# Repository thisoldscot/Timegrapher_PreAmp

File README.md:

# Timegrapher PreAmp

[![CC BY-NC-SA 4.0][cc-by-nc-sa-shield]][cc-by-nc-sa]

## About the Project

|  |
| :-----------------------------------------------------------------------------------------------------------: |

Timegrapher PreAmp is the **through-hole** piezo preamplifier board for the
Timegrapher Studio wristwatch timegrapher. It conditions the faint escapement
signal from the piezo pickup and feeds the I²S ADC on the
[carrier HAT](https://github.com/thisoldscot/Timegrapher_Hat). This is the
hand-solderable variant; an SMD version lives in
[Timegrapher_PreAmpSMD](https://github.com/thisoldscot/Timegrapher_PreAmpSMD).
Designed in KiCad. See [DESIGN.md](DESIGN.md) and [BOM.md](BOM.md).

---

## Repository Contents

This repository contains the KiCad design and production files:

- **`TimegrapherPreamp.kicad_pro` / `.kicad_sch` / `.kicad_pcb`** — KiCad project.
- **`Preamp.kicad_sym` / `sym-lib-table`** — schematic symbols.
- **`Production/`** — Gerbers, drill files, and the fabrication zip.
- **`TimegrapherPreamp.step`** — 3D model of the assembled board.
- **`TimegrapherPreamp_sch.pdf`** — schematic PDF.
- **`gen_sch.py` / `gen_pcb.py`** — scripts used to generate the design.
- **`BOM.md`** — bill of materials. **`DESIGN.md`** — design notes.

Refer to the `CHANGELOG.md` for details about updates between versions.

---

## Timegrapher project

Timegrapher Studio is split across several repositories:

| Repository | Contents |
| --- | --- |
| [Timegrapher_OS](https://github.com/thisoldscot/Timegrapher_OS) | Desktop application |
| [Timegrapher_App](https://github.com/thisoldscot/Timegrapher_App) | Mobile companion app |
| [Timegrapher_Firmware](https://github.com/thisoldscot/Timegrapher_Firmware) | ESP32 device firmware |
| [Timegrapher_Hat](https://github.com/thisoldscot/Timegrapher_Hat) | Carrier HAT (PCB) |
| [Timegrapher_PreAmp](https://github.com/thisoldscot/Timegrapher_PreAmp) | Piezo preamp (through-hole) (this repo) |
| [Timegrapher_PreAmpSMD](https://github.com/thisoldscot/Timegrapher_PreAmpSMD) | Piezo preamp (SMD) |
| [Timegrapher_Stand](https://github.com/thisoldscot/Timegrapher_Stand) | 3D-printed stand & fixtures |

---

## Learn More

### Documentation

Build notes, BOM, and assembly guides can be found here:
[ThisOldScot Docs](https://thisoldscot.com)
<!-- TODO: replace with the real docs URL when live -->

### ThisOldScot Community

ThisOldScot Community is a great space for the maker community — get answers to
your questions and solutions for our projects there.
<!-- TODO: add the real community/forum URL -->

### ThisOldScot Discord

Another option to get help and advice from other makers via the ThisOldScot Discord.
<!-- TODO: add the real Discord invite URL -->

---

## Contributing

Contributions are welcome! Here's how you can get involved:

- Submit pull requests to enhance the design or fix issues.
- Report bugs or problems by opening an issue.

We encourage community collaboration to make this project even better.

---

## About ThisOldScot

[ThisOldScot](https://thisoldscot.com) enjoys designing and making electronic
products and projects for enthusiasts, from hobbyists to professionals — boards,
sensors, hobby equipment, and anything else that catches my interest. Every
project is designed in-house and built on open-source hardware and software.

---

# Support the team
We :heart: doing research. New hardware (e.g. oscilloscopes, logic analysers,
servos, PCBs) is costly. Feel free to support us and accelerate our research.

Dev | ThisOldScot |
--- | --- |
Buy me a coffee |  |
Ko-fi |  |
<!-- TODO: add the real Buy Me a Coffee / Ko-fi URLs -->

---

## License

This work is licensed under a Creative Commons Attribution-NonCommercial-ShareAlike
4.0 International License. Read more in the LICENSE file located in this repository.

Shield: [![CC BY-NC-SA 4.0][cc-by-nc-sa-shield]][cc-by-nc-sa]

[![CC BY-NC-SA 4.0][cc-by-nc-sa-image]][cc-by-nc-sa]

[cc-by-nc-sa]: http://creativecommons.org/licenses/by-nc-sa/4.0/
[cc-by-nc-sa-image]: https://licensebuttons.net/l/by-nc-sa/4.0/88x31.png
[cc-by-nc-sa-shield]: https://img.shields.io/badge/License-CC%20BY--NC--SA%204.0-lightgrey.svg

---

**Disclaimer:**

These designs are provided "AS IS", without warranty of any kind, either expressed
or implied. The entire quality and performance of what you do with the contents of
this repository is your responsibility. In no event will ThisOldScot be liable for
any damages or losses arising out of the use or inability to use the contents of
this repository.

> [!WARNING]
> Use responsibly and at your own risk.

---

## Have fun!

Thank you for your support from your fellow makers at ThisOldScot.

Happy Making!

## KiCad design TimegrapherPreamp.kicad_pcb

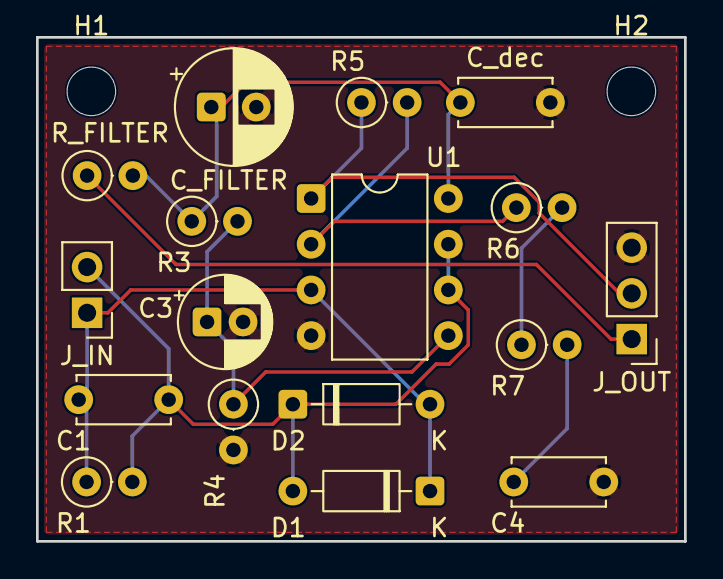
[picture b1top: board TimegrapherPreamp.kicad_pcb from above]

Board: 2 copper layers, 36.0 x 28.0 mm, 19 parts (0 on the bottom side), 10 nets.

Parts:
C1: 100pF; C_Disc_D5.0mm_W2.5mm_P5.00mm
C3: 10uF; CP_Radial_D5.0mm_P2.00mm
C4: 100nF; C_Disc_D5.0mm_W2.5mm_P5.00mm
C_FILTER: 100uF; CP_Radial_D6.3mm_P2.50mm
C_dec: 100nF; C_Disc_D5.0mm_W2.5mm_P5.00mm
D1, D2: 1N4148; D_DO-35_SOD27_P7.62mm_Horizontal
H1, H2: M2.5; MountingHole_2.7mm_M2.5
J_IN: Piezo; PinHeader_1x02_P2.54mm_Vertical
J_OUT: Preamp; PinHeader_1x03_P2.54mm_Vertical
R1: 4.7M; R_Axial_DIN0207_L6.3mm_D2.5mm_P2.54mm_Vertical
R3, R4, R6: 10k; R_Axial_DIN0207_L6.3mm_D2.5mm_P2.54mm_Vertical
R5: 100k; R_Axial_DIN0207_L6.3mm_D2.5mm_P2.54mm_Vertical
R7: 1k; R_Axial_DIN0207_L6.3mm_D2.5mm_P2.54mm_Vertical
R_FILTER: 10R; R_Axial_DIN0207_L6.3mm_D2.5mm_P2.54mm_Vertical
U1: MCP602-I/P; DIP-8_W7.62mm

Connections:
+5V: J_OUT.1, R_FILTER.1
+5VF: C_FILTER.1, C_dec.1, R3.1, R_FILTER.2, U1.8
AUDIO_OUT: J_OUT.2, R5.1, U1.1
FB: R5.2, R6.1, U1.2
GLEG: R6.2, R7.1
GLEGC: C4.1, R7.2
GND: C3.2, C4.2, C_FILTER.2, C_dec.2, J_OUT.3, R4.2, U1.4
PZ: C1.1, D1.1, D2.2, J_IN.1, R1.1, U1.3
VREF: C1.2, D1.2, D2.1, J_IN.2, R1.2, U1.6, U1.7
VREF_DIV: C3.1, R3.2, R4.1, U1.5
